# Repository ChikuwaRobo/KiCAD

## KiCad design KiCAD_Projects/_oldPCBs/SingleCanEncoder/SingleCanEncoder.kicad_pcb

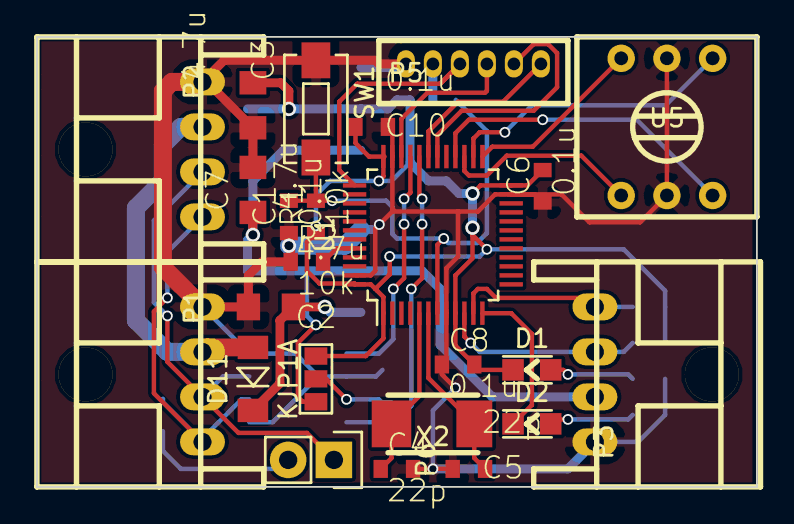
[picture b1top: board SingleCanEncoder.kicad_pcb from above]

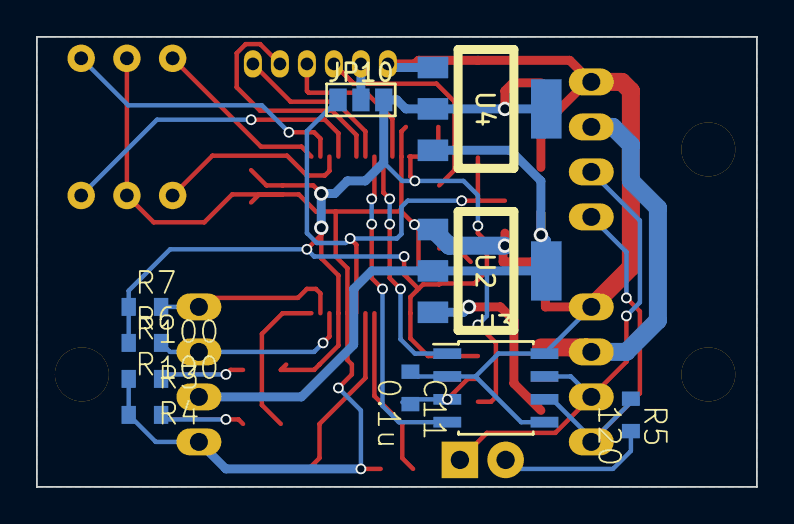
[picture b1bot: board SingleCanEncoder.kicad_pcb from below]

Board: 2 copper layers, 40.0 x 25.0 mm, 34 parts (10 on the bottom side), 29 nets.

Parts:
C1, C6, C8, C10, C11: 0.1u; C1608_WP
C2, C3, C7: 4.7u; C2012
C4, C5: 22p; C1608_WP
D1, D2: LED; LED_0805
D11: DIODE; MiniMELF_Standard
JP1, JP10: JUMPER3; GS3
P1, P2, P3: CONN_01X04; XA_4LC
P5: CONN_01X06; ZH_6T
P6: CONN_01X02; Pin_Header_Straight_1x02
R1, R2: 10k; C1608_WP
R3, R4: 100; C1608_WP
R5: 120; C1608_WP
R6, R7: R; C1608_WP
SW1: SW_PUSH; SW_SPST_EVQPE1
U1: STM32F103_48; LQFP-48_7x7mm_Pitch0.5mm
U2: NCP1117ST33T3G; SOT-223_reg
U3: MAX3051; SOIC-8_3.9x4.9mm_Pitch1.27mm
U4: NCP1117ST50T3G; SOT-223_reg
U5: SW_ROTARY_16; rotary_0F
X2: CRYSTAL; ABM3_2pads

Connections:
+3.3V: C3.1, C6.2, C8.2, C10.2, D1.1, JP1.3, JP10.3, R1.1, R6.1, R7.1, U1.1, U1.9, U1.24, U1.36, U1.48, U4.2
+5V: C7.1, JP1.1, P3.2, U2.2, U4.3
+12V: C2.1, D11.1, U2.3
/BOOT0: R2.2, U1.44
/CAN_H: P1.3, P2.3, P6.1, U3.7
/CAN_L: P1.4, P2.4, R5.1, U3.6
/CAN_RX: U1.32, U3.4
/CAN_TX: U1.33, U3.1
/ENC_A: P3.3, R6.2, U1.10
/ENC_B: P3.4, R7.2, U1.11
/LED: D2.1, U1.12
/NRST: C1.2, JP10.1, R1.2, SW1.2, U1.7
/OSC_IN: C4.1, U1.5, X2.1
/OSC_OUT: C5.1, U1.6, X2.2
/SEL_1: U1.25, U5.3
/SEL_2: U1.26, U5.1
/SEL_4: U1.27, U5.4
/SEL_8: U1.28, U5.6
/SWCLK: P5.3, U1.37
/SWDIO: P5.4, U1.34
/USART_RX: P5.6, U1.31
/USART_TX: P5.5, U1.30
GND: C1.1, C2.2, C3.2, C4.2, C5.2, C6.1, C7.2, C8.1, C10.1, C11.1, P1.1, P2.1, P3.1, P5.1, R2.1, R3.2, R4.2, SW1.1, U1.8, U1.23, U1.35, U1.47, U2.1, U3.2, U3.5, U3.8, U4.1, U5.2, U5.5
unnamed: C11.2, JP1.2, U3.3
unnamed: D1.2, R3.1
unnamed: D2.2, R4.1
unnamed: D11.2, P1.2, P2.2
unnamed: JP10.2, P5.2
unnamed: P6.2, R5.2

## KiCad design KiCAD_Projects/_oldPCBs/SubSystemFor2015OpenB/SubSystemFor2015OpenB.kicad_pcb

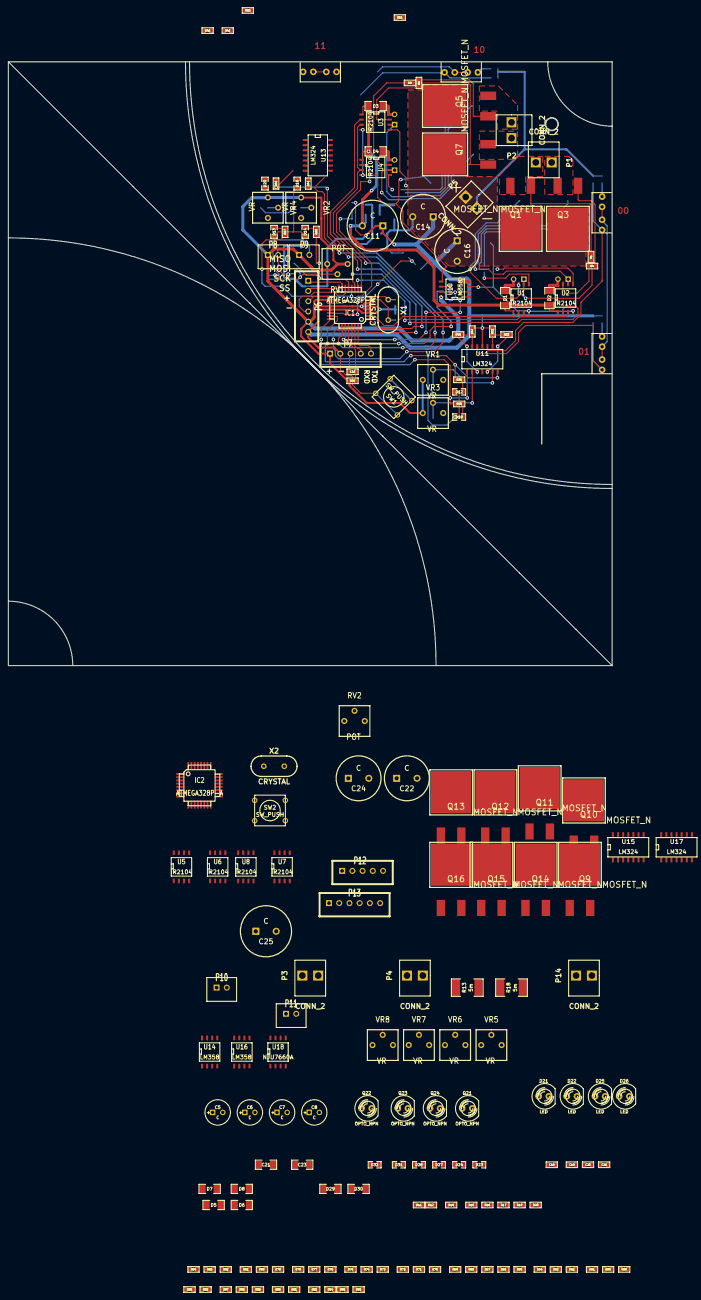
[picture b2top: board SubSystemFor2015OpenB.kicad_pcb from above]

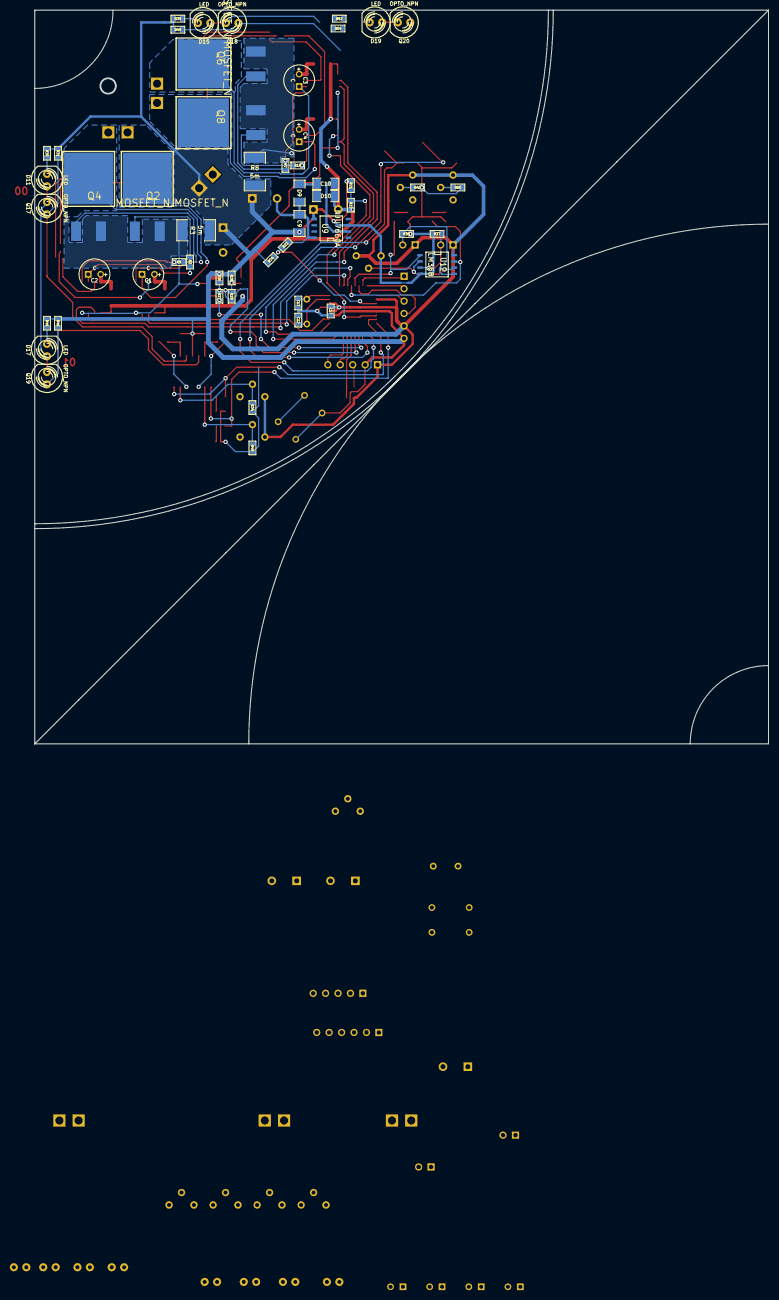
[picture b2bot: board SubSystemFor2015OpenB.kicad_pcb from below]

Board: 2 copper layers, 150.0 x 150.0 mm, 224 parts (53 on the bottom side), 175 nets.

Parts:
C1, C2, C3, C4, C5, C6, C7, C8: C; C1V6.3
C9, C10, C21, C23: C; SM1206
C11, C25: C; C2V12
C12, C13, C19, C20: 22p; SM0603
C14, C16, C22, C24: C; C2V10
C15, C17, C18, C26: 0.1u; SM0603
D1, D2, D3, D4, D5, D6, D7, D8, D9, D10, D29, D30: DIODE; SM1206
D11, D15, D17, D19, D21, D22, D25, D26: LED; LED-5MM
D12, D13, D14, D16, D18, D20, D23, D24, D27, D28, D31, D32: LED; SM0805
IC1, IC2: ATMEGA328P-A; TQFP32
P1, P2, P3, P4, P5, P14: CONN_2; VH
P6, P13: CONN_6; XH6
P7, P12: CONN_5; XH5
P8, P9, P10, P11: CONN_2; XH2
Q1, Q2, Q3, Q4, Q5, Q6, Q7, Q8, Q9, Q10, Q11, Q12, Q13, Q14, Q15, Q16: MOSFET_N; TO263
Q17, Q18, Q19, Q20, Q21, Q22, Q23, Q24: OPTO_NPN; LED-5MM
R1, R2, R4, R5, R6, R7, R9, R10, R11, R12, R14, R15, R16, R17, R19, R20: 100; SM0603
R3, R8, R13, R18: 5m; SM2512
R21, R27, R29, R34, R43, R49, R55, R62, R69, R70, R74, R87, R88, R94: 100k; SM0603
R22, R95: 470k; SM0603
R23, R24, R25, R89, R90, R96: 10k; SM0603
R26, R28, R30, R32, R35, R39, R41, R44, R45, R47, R50, R51, R53, R56, R57, R58, R59, R60, R61, R65, R66, R71, R72, R73, R75, R76, R80, R82, R85, R86, R91, R92: 1k; SM0603
R31, R37, R38, R40, R46, R52, R63, R64, R77, R78, R79, R81: 4k7; SM0603
R33, R42, R48, R54, R67, R68, R83, R84: 3k3; SM0603
RV1, RV2: POT; RV2sq
SW1, SW2: SW_PUSH; SW_PUSH_SMALL
U1, U2, U3, U4, U5, U6, U7, U8: IR2104; SO8N
U9, U18: NJU7660A; SO8N
U10, U12, U14, U16: LM358; SO8N
U11, U13, U15, U17: LM324; SO14N
VR1, VR2, VR3, VR4, VR5, VR6, VR7, VR8: VR; RV2sq
X1, X2: CRYSTAL; HC-49V

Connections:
+5V: C17.1, C18.1, D11.1, D15.1, D17.1, D19.1, D21.1, D22.1, D25.1, D26.1, IC1.4, IC1.6, IC1.18, IC1.20, IC2.4, IC2.6, IC2.18, IC2.20, P6.5, P7.1, P8.1, P9.1, P10.1, P11.1, P12.1, P13.5, Q17.3, Q18.3, Q19.3, Q20.3, R25.1, R96.1, RV1.1, RV2.1, U10.8, U11.4, U12.8, U13.4, U14.8, U15.4, U16.8, U17.4, VR1.1, VR2.1, VR3.1, VR4.1, VR5.1, VR6.1, VR7.1, VR8.1
+BATT: C9.1, C14.1, C16.1, C21.1, C22.1, C24.1, D9.1, D29.1, P5.1, P14.1, Q1.D, Q3.D, Q5.D, Q7.D, Q9.D, Q11.D, Q13.D, Q15.D, R23.1, R89.1, U9.8, U18.8
BatteryVoltage0: IC1.19, R23.2, R24.2
BatteryVoltage1: IC2.19, R89.2, R90.2
Current0: Q2.S, Q4.S, R3.1, U1.4, U2.4, U10.3
Current1: Q6.S, Q8.S, R8.1, U3.4, U4.4, U10.5
Current2: Q10.S, Q12.S, R13.1, U5.4, U6.4, U14.3
Current3: Q14.S, Q16.S, R18.1, U7.4, U8.4, U14.5
CurrentTTL0: IC1.27, R27.1, U10.1
CurrentTTL1: IC1.28, R29.1, U10.7
CurrentTTL2: IC2.27, R62.1, U14.1
CurrentTTL3: IC2.28, R74.1, U14.7
GND: C9.2, C11.2, C12.1, C13.1, C14.2, C16.2, C17.2, C18.2, C19.1, C20.1, C21.2, C22.2, C24.2, C25.2, D12.2, D13.2, D14.2, D16.2, D18.2, D20.2, D23.2, D24.2, D27.2, D28.2, D31.2, D32.2, IC1.3, IC1.5, IC1.21, IC2.3, IC2.5, IC2.21, P5.2, P6.6, P7.2, P12.2, P13.6, P14.2, R3.2, R8.2, R13.2, R18.2, R21.2, R24.1, R26.2, R28.2, R30.2, R31.2, R32.2, R34.2, R37.2, R38.1, R39.2, R40.2, R41.2, R43.2, R45.2, R46.2, R47.2, R49.2, R51.2, R52.2, R53.2, R55.2, R59.2, R60.2, R61.2, R63.2, R64.2, R65.2, R66.2, R69.2, R70.2, R71.2, R75.2, R76.2, R77.2, R78.2, R79.1, R80.2, R81.2, R82.2, R87.2, R88.2, R90.1, R94.2, RV1.3, RV2.3, SW1.1, SW2.1, U9.3, U9.5, U10.4, U11.11, U12.4, U13.11, U14.4, U15.11, U16.4, U17.11, U18.3, U18.5
GateDrive0: C11.1, D1.1, D2.1, D3.1, D4.1, D10.2, R22.1, U1.1, U2.1, U3.1, U4.1
GateDrive1: C25.1, D5.1, D6.1, D7.1, D8.1, D30.2, R95.1, U5.1, U6.1, U7.1, U8.1
GateDriveVoltage0: IC1.22, R21.1, R22.2
GateDriveVoltage1: IC2.22, R94.1, R95.2
IN00: IC1.2, U1.2
IN01: IC1.11, U2.2
IN10: IC1.32, U3.2
IN11: IC1.1, U4.2
IN20: IC2.2, U5.2
IN21: IC2.11, U6.2
IN30: IC2.32, U7.2
IN31: IC2.1, U8.2
Line00: IC1.23, R35.1, U11.7
Line01: IC1.24, R50.1, U11.1
Line10: IC1.25, R44.1, U13.7
Line11: IC1.26, R56.1, U13.1
Line20: IC2.23, R73.1, U15.7
Line21: IC2.24, R72.1, U15.1
Line30: IC2.25, R91.1, U17.7
Line31: IC2.26, R92.1, U17.1
MISO0: IC1.16, P6.2
MISO1: IC2.16, P13.2
MOSI0: IC1.15, P6.1
MOSI1: IC2.15, P13.1
unnamed: C23.2, U18.2
unnamed: R59.1, R62.2, U14.2
unnamed: P11.2, R81.1, U16.5
unnamed: P10.2, R79.2, U16.3
unnamed: C20.2, IC2.8, X2.1
unnamed: C19.2, IC2.7, X2.2
unnamed: R71.1, R74.2, U14.6
unnamed: Q20.1, R52.1, U13.12
unnamed: R53.1, R54.2, U13.13
unnamed: D20.1, R56.2
unnamed: R49.1, U11.2, VR3.2
unnamed: R48.1, U11.3, U11.14
unnamed: Q19.1, R46.1, U11.12
unnamed: R47.1, R48.2, U11.13
unnamed: D18.1, R50.2
unnamed: D17.2, R45.1
unnamed: D19.2, R51.1
unnamed: D13.1, R57.2
unnamed: D14.1, R58.2
unnamed: R54.1, U13.3, U13.14
unnamed: R55.1, U13.2, VR4.2
unnamed: C23.1, D29.2, D30.1
unnamed: Q17.1, R31.1, U11.10
unnamed: Q18.1, R40.1, U13.10
unnamed: Q24.1, R78.1, U17.12
unnamed: R82.1, R84.2, U17.13
unnamed: D32.1, R92.2
unnamed: D26.2, R76.1
unnamed: R84.1, U17.3, U17.14
unnamed: R88.1, U17.2, VR8.2
unnamed: R67.1, U15.3, U15.14
unnamed: R69.1, U15.2, VR5.2
unnamed: Q21.1, R63.1, U15.12
unnamed: R65.1, R67.2, U15.13
unnamed: D23.1, R72.2
unnamed: D21.2, R60.1
unnamed: D27.1, R85.2
unnamed: D28.1, R86.2
unnamed: Q23.1, R77.1, U17.10
unnamed: R68.1, U15.5, U15.8
unnamed: R66.1, R68.2, U15.9
unnamed: Q22.1, R64.1, U15.10
unnamed: D24.1, R73.2
unnamed: R87.1, U17.6, VR7.2
unnamed: R83.1, U17.5, U17.8
unnamed: R80.1, R83.2, U17.9
unnamed: D31.1, R91.2
unnamed: D25.2, R75.1
unnamed: D22.2, R61.1
unnamed: R70.1, U15.6, VR6.2
unnamed: C10.2, U9.2
unnamed: C8.1, D8.2, U8.8
unnamed: C8.2, P4.1, Q15.S, Q16.D, U8.6
unnamed: Q15.G, R19.1
unnamed: R20.2, U8.5
unnamed: Q16.G, R20.1
unnamed: R19.2, U8.7
unnamed: R28.1, R29.2, U10.6
unnamed: R26.1, R27.2, U10.2
unnamed: C10.1, D9.2, D10.1
unnamed: C13.2, IC1.8, X1.1
unnamed: C12.2, IC1.7, X1.2
unnamed: Q6.G, R7.1
unnamed: R7.2, U3.5
unnamed: Q5.G, R6.1
unnamed: R6.2, U3.7
unnamed: C3.2, P2.2, Q5.S, Q6.D, U3.6
unnamed: Q7.G, R9.1
unnamed: R10.2, U4.5
unnamed: Q8.G, R10.1
unnamed: R9.2, U4.7
unnamed: C4.2, P2.1, Q7.S, Q8.D, U4.6
unnamed: C3.1, D3.2, U3.8
unnamed: C2.2, P1.1, Q3.S, Q4.D, U2.6
unnamed: C1.2, P1.2, Q1.S, Q2.D, U1.6
unnamed: Q1.G, R1.1
unnamed: C1.1, D1.2, U1.8
unnamed: Q4.G, R5.1
unnamed: R2.2, U1.5
unnamed: Q2.G, R2.1
unnamed: R1.2, U1.7
unnamed: Q3.G, R4.1
unnamed: C2.1, D2.2, U2.8
unnamed: R5.2, U2.5
unnamed: R4.2, U2.7
unnamed: Q14.G, R17.1
unnamed: C7.2, P4.2, Q13.S, Q14.D, U7.6
unnamed: Q13.G, R16.1
unnamed: C6.2, P3.1, Q11.S, Q12.D, U6.6
unnamed: Q11.G, R14.1
unnamed: C6.1, D6.2, U6.8
unnamed: C7.1, D7.2, U7.8
unnamed: R17.2, U7.5
unnamed: R16.2, U7.7
unnamed: C5.1, D5.2, U5.8
unnamed: Q10.G, R12.1
unnamed: Q9.G, R11.1
unnamed: C5.2, P3.2, Q9.S, Q10.D, U5.6
unnamed: C4.1, D4.2, U4.8
unnamed: R15.2, U6.5
unnamed: Q12.G, R15.1
unnamed: R14.2, U6.7
unnamed: R11.2, U5.7
unnamed: R12.2, U5.5
unnamed: R41.1, R42.2, U13.9
unnamed: R42.1, U13.5, U13.8
unnamed: R43.1, U13.6, VR2.2
unnamed: D16.1, R44.2
unnamed: D15.2, R39.1
unnamed: R34.1, U11.6, VR1.2
unnamed: R33.1, U11.5, U11.8
unnamed: R32.1, R33.2, U11.9
unnamed: D11.2, R30.1
unnamed: D12.1, R35.2
unnamed: P8.2, R37.1, U12.3
unnamed: P9.2, R38.2, U12.5
PWM0: IC1.10, U1.3, U2.3
PWM1: IC1.9, U3.3, U4.3
PWM2: IC2.10, U5.3, U6.3
PWM3: IC2.9, U7.3, U8.3
RST: C15.1, IC1.29, R25.2, SW1.2
RST1: C26.1, IC2.29, R96.2, SW2.2
RSTex: C15.2, P7.3
RSTex1: C26.2, P12.3
RXD: IC1.30, P7.4
RXD1: IC2.30, P12.4
SCK0: IC1.17, P6.3
SCK1: IC2.17, P13.3
SS0: IC1.14, P6.4
SS1: IC2.14, P13.4
TXD: IC1.31, P7.5
TXD1: IC2.31, P12.5
Temperature0: IC1.13, R58.1, U12.1
Temperature1: IC1.12, R57.1, U12.7
Temperature2: IC2.13, R86.1, U16.7
Temperature3: IC2.12, R85.1, U16.1
Threshold0: RV1.2, U12.2, U12.6
Threshold1: RV2.2, U16.2, U16.6

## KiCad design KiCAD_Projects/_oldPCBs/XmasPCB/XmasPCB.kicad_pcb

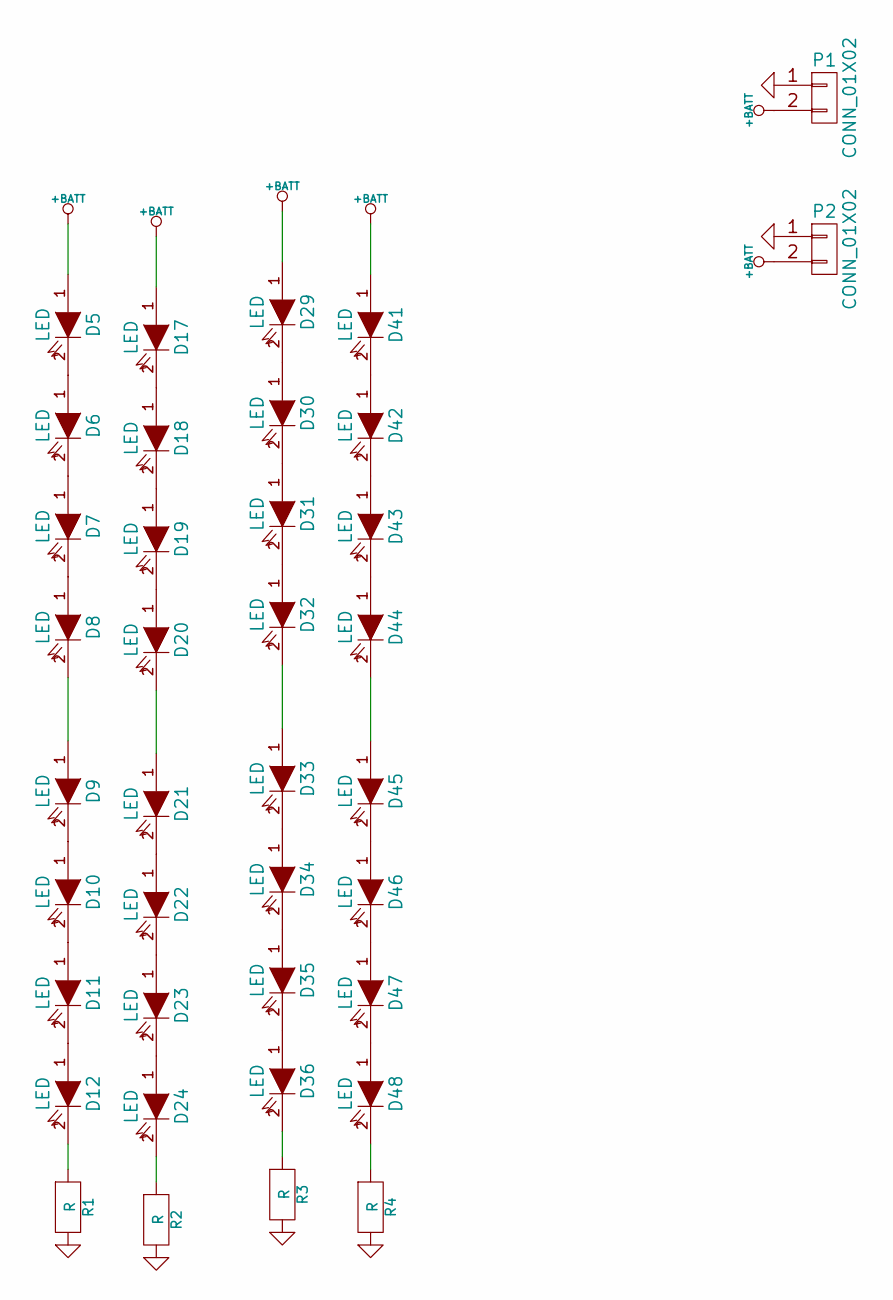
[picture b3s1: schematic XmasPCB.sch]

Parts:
D5, D6, D7, D8, D9, D10, D11, D12, D17, D18, D19, D20, D21, D22, D23, D24, D29, D30, D31, D32, D33, D34, D35, D36, D41, D42, D43, D44, D45, D46, D47, D48: LED; LED_0805
P1: CONN_01X02; DEANS_T_M
P2: CONN_01X02; DEANS_T_F
R1, R2, R3, R4: R; C3225

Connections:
+BATT: D5.1 (A), D17.1 (A), D29.1 (A), D41.1 (A), P1.2, P2.2
GND: P1.1, P2.1, R1.2, R2.2, R3.2, R4.2
unnamed: D5.2 (K), D6.1 (A)
unnamed: D6.2 (K), D7.1 (A)
unnamed: D7.2 (K), D8.1 (A)
unnamed: D8.2 (K), D9.1 (A)
unnamed: D9.2 (K), D10.1 (A)
unnamed: D10.2 (K), D11.1 (A)
unnamed: D11.2 (K), D12.1 (A)
unnamed: D12.2 (K), R1.1
unnamed: D17.2 (K), D18.1 (A)
unnamed: D18.2 (K), D19.1 (A)
unnamed: D19.2 (K), D20.1 (A)
unnamed: D20.2 (K), D21.1 (A)
unnamed: D21.2 (K), D22.1 (A)
unnamed: D22.2 (K), D23.1 (A)
unnamed: D23.2 (K), D24.1 (A)
unnamed: D24.2 (K), R2.1
unnamed: D29.2 (K), D30.1 (A)
unnamed: D30.2 (K), D31.1 (A)
unnamed: D31.2 (K), D32.1 (A)
unnamed: D32.2 (K), D33.1 (A)
unnamed: D33.2 (K), D34.1 (A)
unnamed: D34.2 (K), D35.1 (A)
unnamed: D35.2 (K), D36.1 (A)
unnamed: D36.2 (K), R3.1
unnamed: D41.2 (K), D42.1 (A)
unnamed: D42.2 (K), D43.1 (A)
unnamed: D43.2 (K), D44.1 (A)
unnamed: D44.2 (K), D45.1 (A)
unnamed: D45.2 (K), D46.1 (A)
unnamed: D46.2 (K), D47.1 (A)
unnamed: D47.2 (K), D48.1 (A)
unnamed: D48.2 (K), R4.1

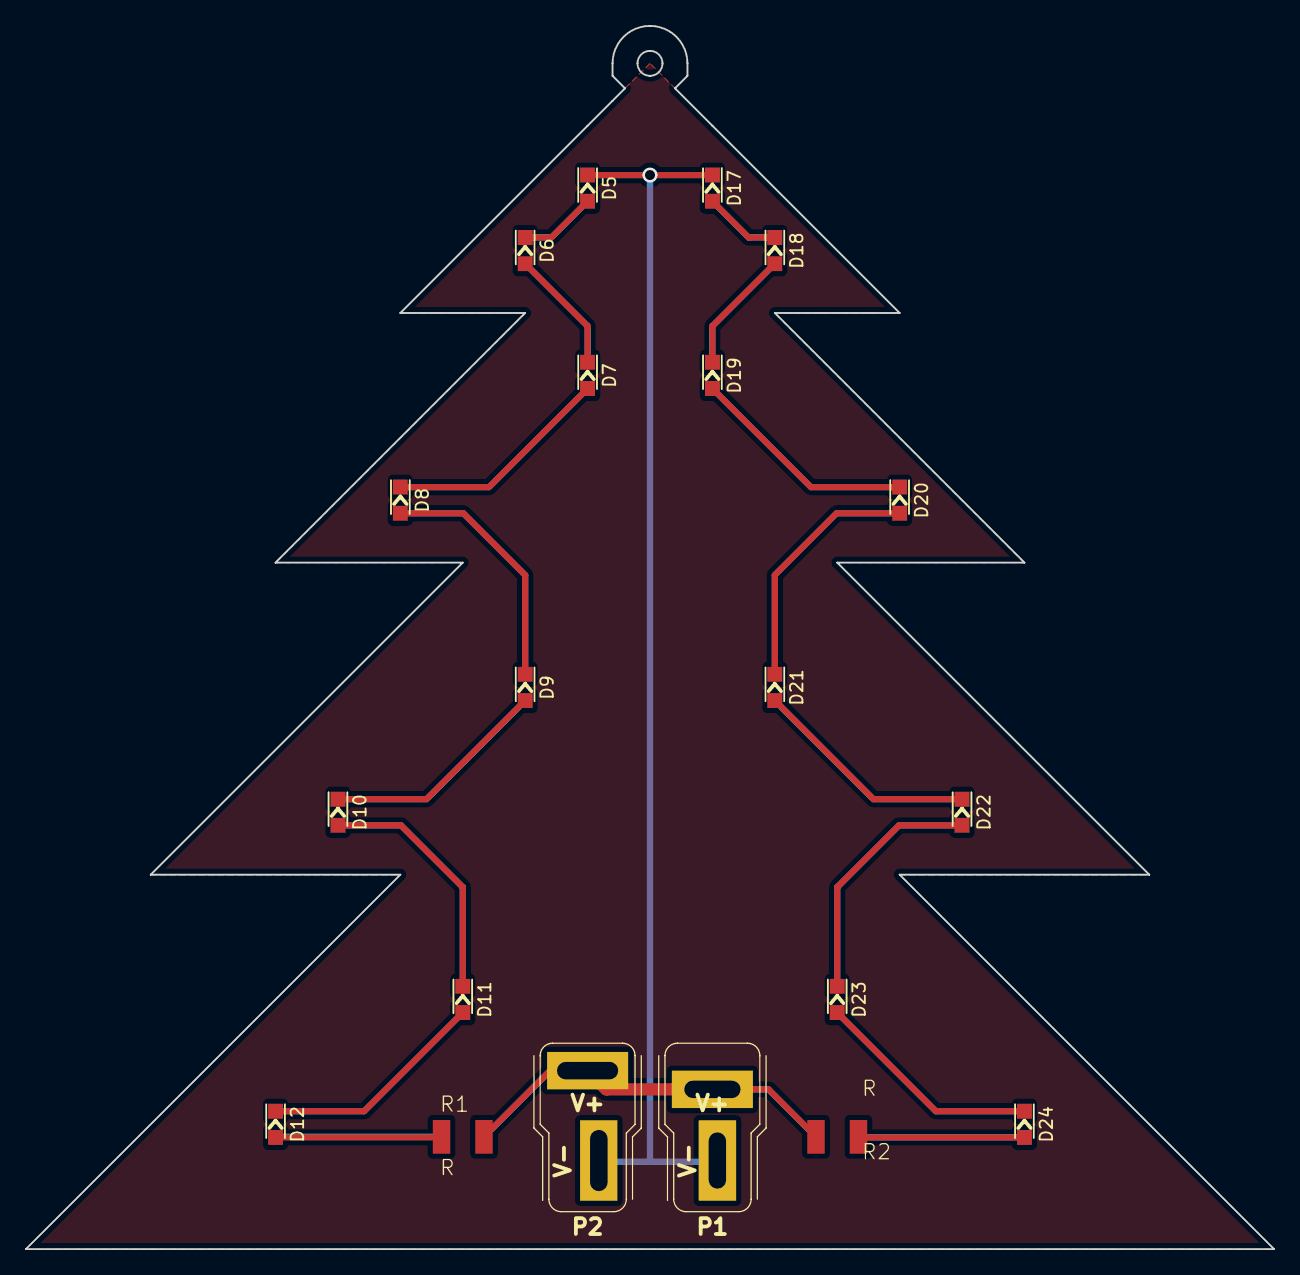
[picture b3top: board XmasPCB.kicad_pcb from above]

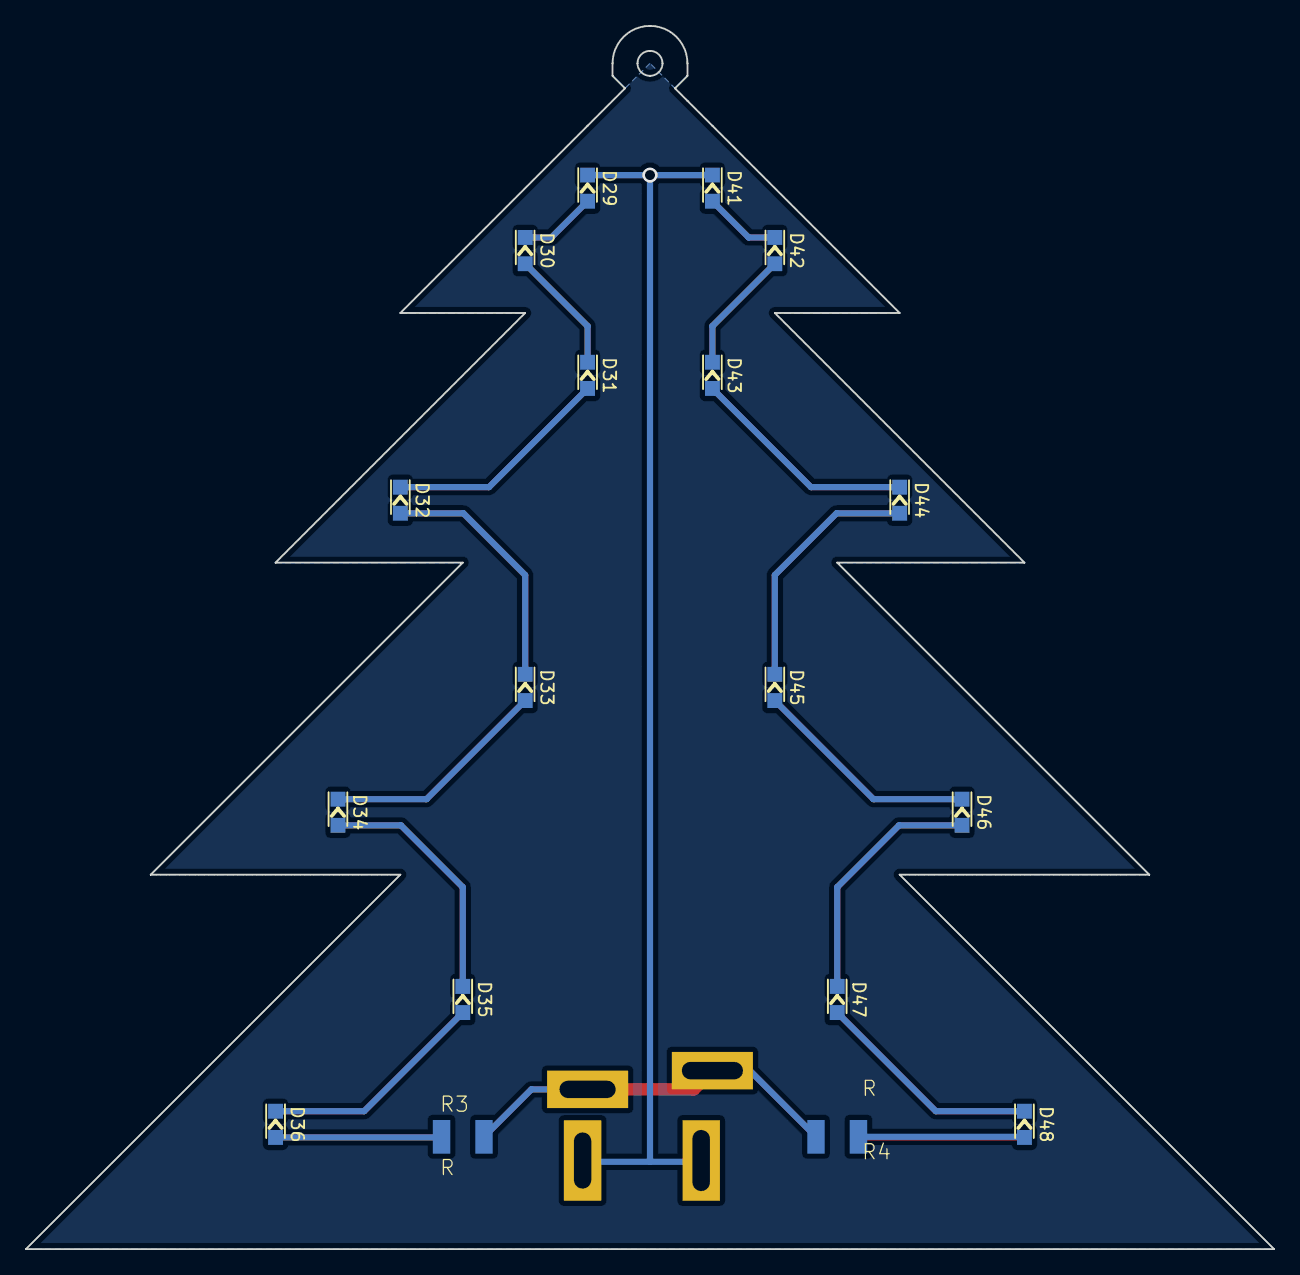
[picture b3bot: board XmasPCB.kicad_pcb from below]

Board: 2 copper layers, 100.0 x 98.0 mm, 38 parts (18 on the bottom side), 34 nets.

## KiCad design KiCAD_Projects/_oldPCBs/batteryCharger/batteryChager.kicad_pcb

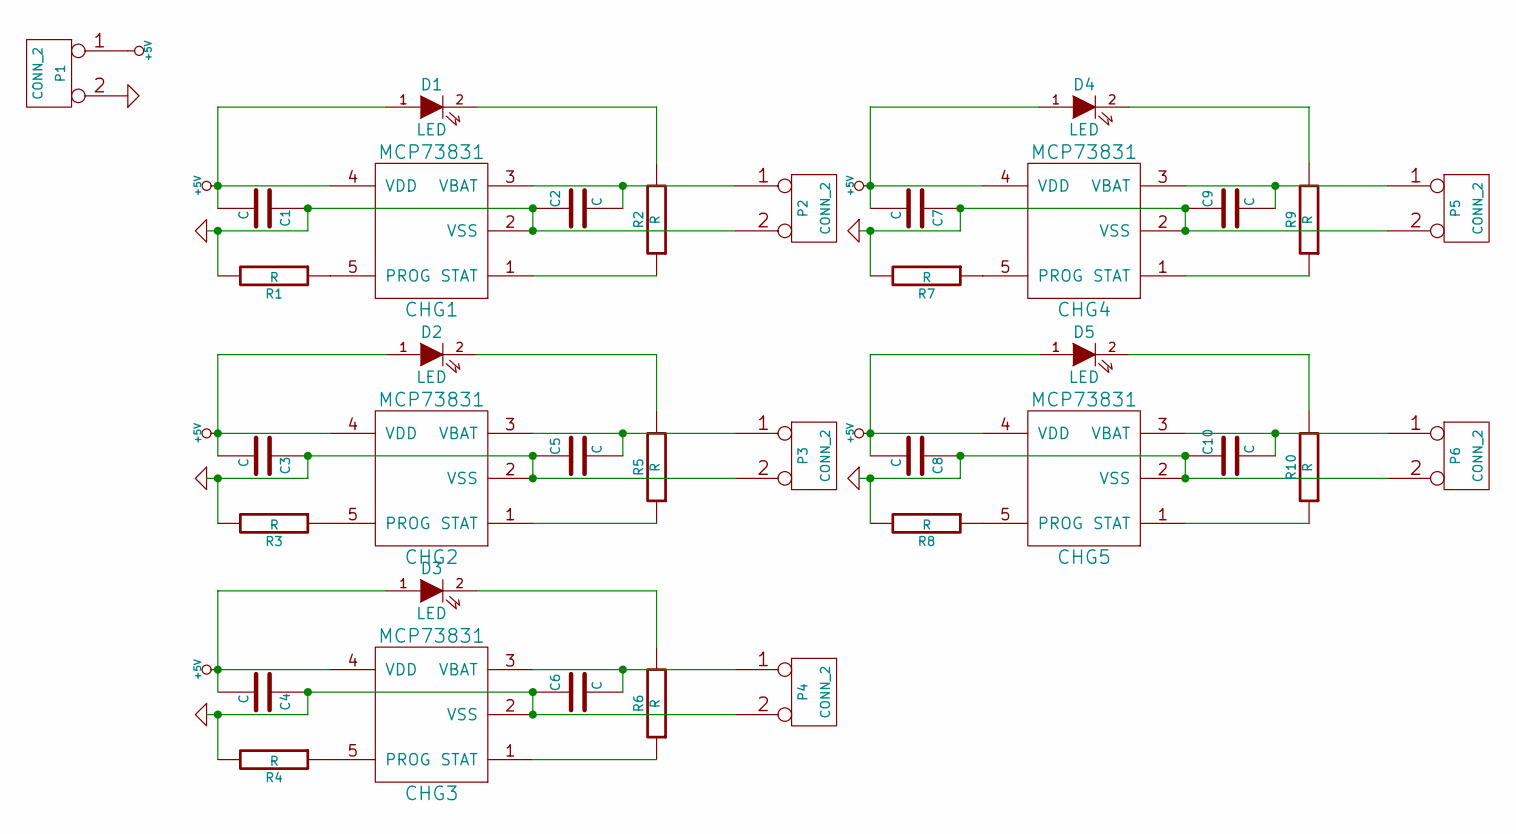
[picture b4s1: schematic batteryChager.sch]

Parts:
C1, C2, C3, C4, C5, C6, C7, C8, C9, C10: C; C_Radial_D5_L11_P2.5
CHG1, CHG2, CHG3, CHG4, CHG5: MCP73831; SOT-23-5
D1, D2, D3, D4, D5: LED; LED-3MM
P1, P2, P3, P4, P5, P6: CONN_2; XA_2T
R1, R2, R3, R4, R5, R6, R7, R8, R9, R10: R; 0204_2f7

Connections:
+5V: C1.2, C3.2, C4.2, C7.2, C8.2, CHG1.4 (VDD), CHG2.4 (VDD), CHG3.4 (VDD), CHG4.4 (VDD), CHG5.4 (VDD), D1.1 (A), D2.1 (A), D3.1 (A), D4.1 (A), D5.1 (A), P1.1
GND: C1.1, C2.1, C3.1, C4.1, C5.1, C6.1, C7.1, C8.1, C9.1, C10.1, CHG1.2 (VSS), CHG2.2 (VSS), CHG3.2 (VSS), CHG4.2 (VSS), CHG5.2 (VSS), P1.2 (PM), P2.2 (PM), P3.2 (PM), P4.2 (PM), P5.2 (PM), P6.2 (PM), R1.2, R3.2, R4.2, R7.2, R8.2
unnamed: C2.2, CHG1.3 (VBAT), P2.1
unnamed: C5.2, CHG2.3 (VBAT), P3.1
unnamed: C6.2, CHG3.3 (VBAT), P4.1
unnamed: C9.2, CHG4.3 (VBAT), P5.1
unnamed: C10.2, CHG5.3 (VBAT), P6.1
unnamed: CHG1.1 (STAT), R2.1
unnamed: CHG1.5 (PROG), R1.1
unnamed: CHG2.1 (STAT), R5.1
unnamed: CHG2.5 (PROG), R3.1
unnamed: CHG3.1 (STAT), R6.1
unnamed: CHG3.5 (PROG), R4.1
unnamed: CHG4.1 (STAT), R9.1
unnamed: CHG4.5 (PROG), R7.1
unnamed: CHG5.1 (STAT), R10.1
unnamed: CHG5.5 (PROG), R8.1
unnamed: D1.2 (K), R2.2
unnamed: D2.2 (K), R5.2
unnamed: D3.2 (K), R6.2
unnamed: D4.2 (K), R9.2
unnamed: D5.2 (K), R10.2

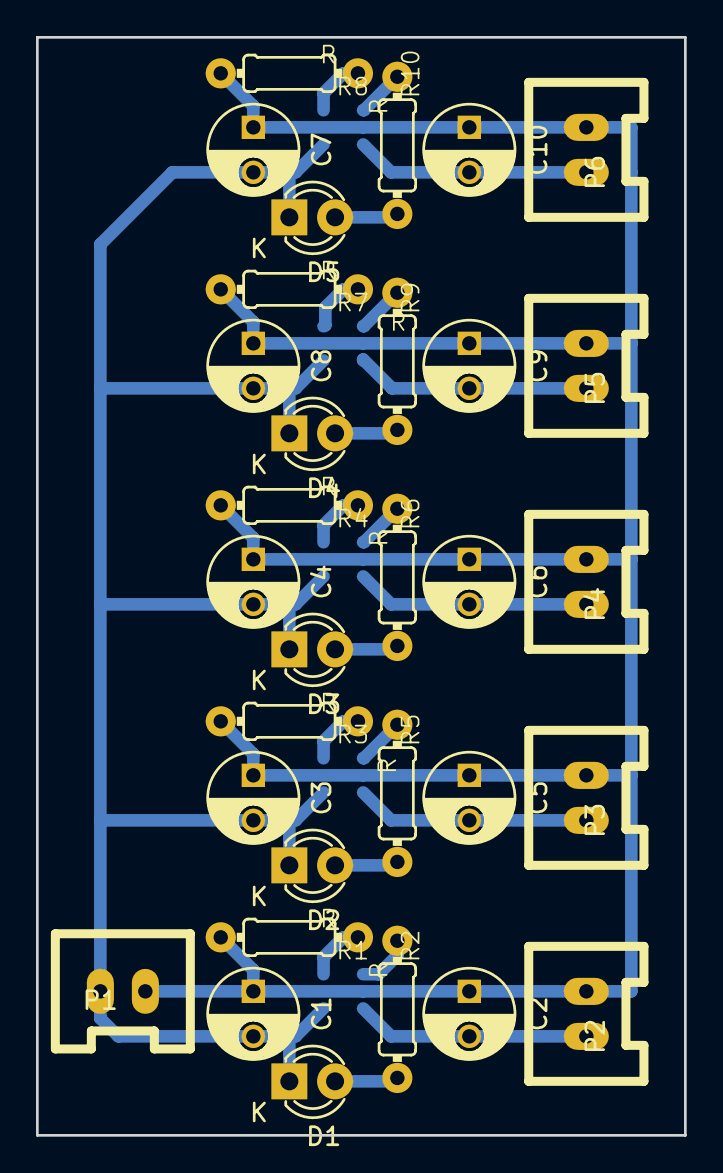
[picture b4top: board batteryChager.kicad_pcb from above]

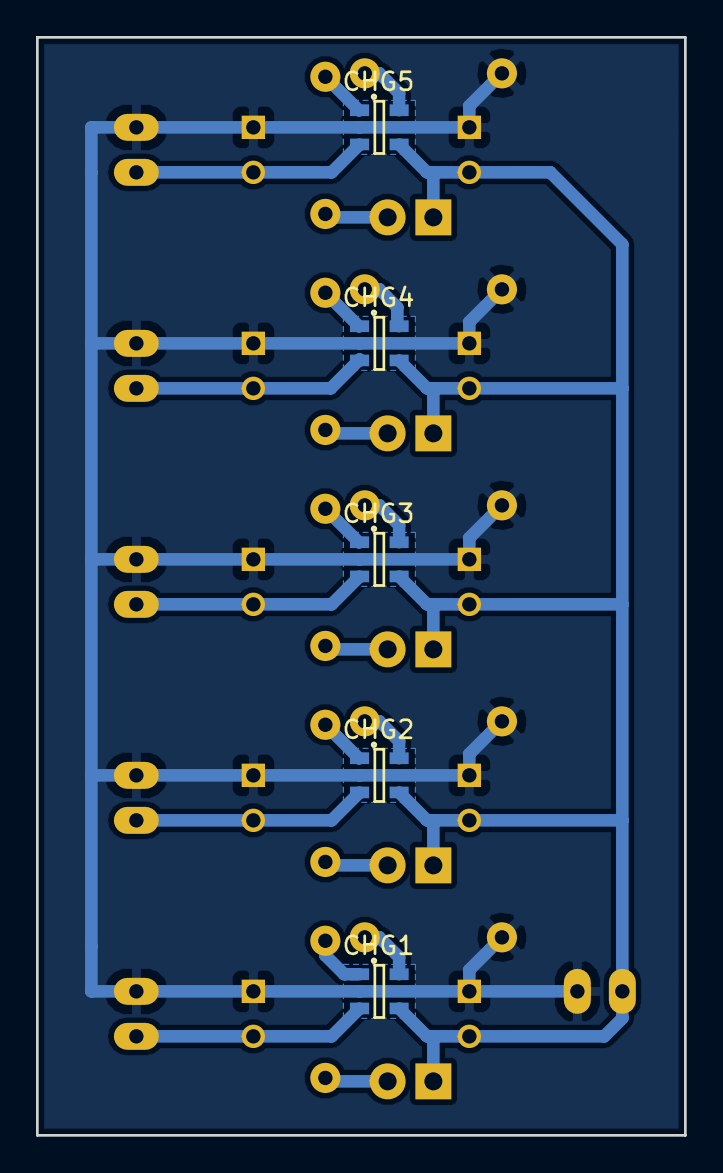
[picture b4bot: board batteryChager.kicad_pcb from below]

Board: 2 copper layers, 36.0 x 61.0 mm, 36 parts (5 on the bottom side), 22 nets.

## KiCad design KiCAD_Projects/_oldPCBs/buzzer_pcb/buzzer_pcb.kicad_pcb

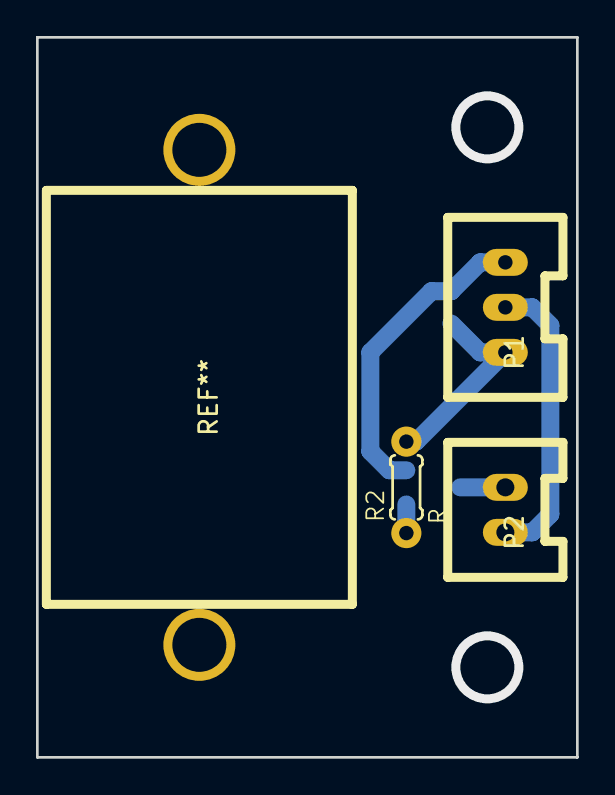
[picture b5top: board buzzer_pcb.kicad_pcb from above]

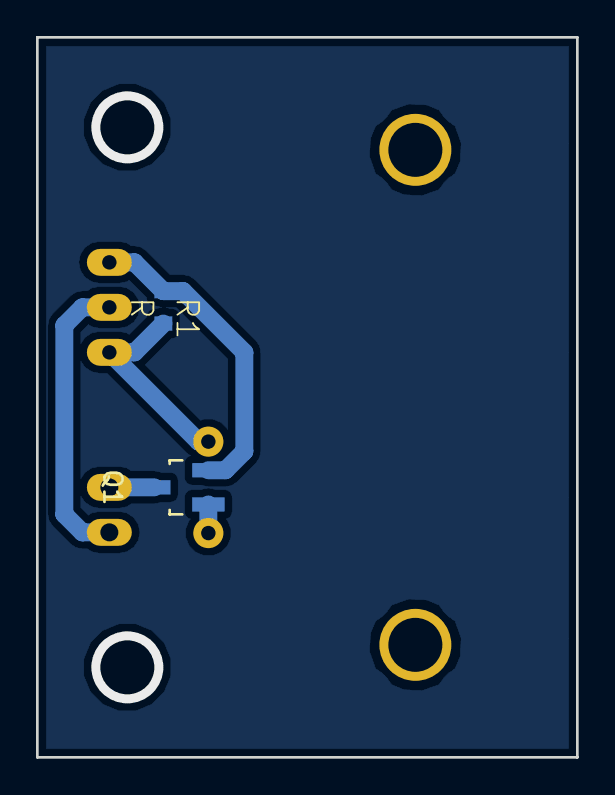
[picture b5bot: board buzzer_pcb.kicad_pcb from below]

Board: 2 copper layers, 30.0 x 40.0 mm, 5 parts (2 on the bottom side), 5 nets.

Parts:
P1: CONN_01X03; XA_3T
P2: CONN_01X02; XA_2T
Q1: MOSFET_N; SOT-23_Handsoldering
R1: R; C1608_WP
R2: R; 0204_2f5

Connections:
+3.3V: P1.2, P2.2
GND: P1.1, Q1.S, R1.1
unnamed: P1.3, R1.2, R2.2
unnamed: P2.1, Q1.D
unnamed: Q1.G, R2.1

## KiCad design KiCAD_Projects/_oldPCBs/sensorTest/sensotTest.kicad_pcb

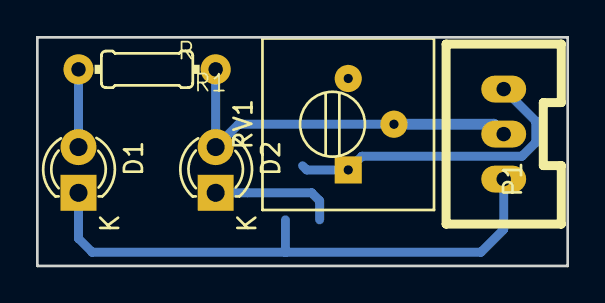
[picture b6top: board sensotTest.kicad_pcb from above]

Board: 2 copper layers, 29.5 x 12.7 mm, 6 parts (1 on the bottom side), 5 nets.

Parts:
D1, D2: LED; LED-3MM
P1: CONN_01X03; XA_3T
Q1: Q_NPN_BEC; SOT-23_Handsoldering
R1: R; 0204_2f7
RV1: POT; Potentiometer_Trimmer-Suntan-TSR-3386P

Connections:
unnamed: D1.1, P1.1, Q1.2
unnamed: D1.2, R1.2
unnamed: D2.1, Q1.1
unnamed: D2.2, P1.2, R1.1, RV1.2
unnamed: P1.3, Q1.3, RV1.1
